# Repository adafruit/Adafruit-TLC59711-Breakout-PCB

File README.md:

# PCB for the Adafruit TLC59711 12-LED PWM breakout board

<a href="http://www.adafruit.com/products/1455"><br/>Click here to purchase one from the Adafruit shop</a>

For all of you out there who want to control 12 channels of PWM, we salute you! We also would like you to check out this breakout board for the TLC59711 PWM driver chip. This chip can control 12 separate channels of 16-bit PWM output. This is the highest-resolution PWM board we've seen! Designed (and ideal) for precision LED control, this board is not good for driving servos. If you need to drive servos, [we have a controller for that over here](http://www.adafruit.com/products/815).

Only two "SPI" pins are required to send data (our Arduino library shows how to to use any digital microcontroller pins). Best of all, the design is completely chainable. As long as there's enough power for all the boards you can chain as many as you'd like, like a little trail of blue PCBs stretching out into the sunset. Each of the 12 outputs are constant-current and open drain. You can drive multiple LEDs in series, with a V+ anode supply of up to 17V. If you want to drive something that requires a digital input, you must use a pullup resistor from the drive pin to your logic level to create the full waveform.

One resistor is used to set the current for each of the outputs, the constant current means that the LED brightness doesn't vary if the power supply dips. We use a 3.3K resistor for about 15mA but you can solder a thru-hole resistor over it if you'd like to change that value. Check the [TLC59711 datasheet](http://www.adafruit.com/datasheets/tlc59711.pdf) for details on resistor-to-current values. There's also a handy on-chip 3.3V regulator which you can use if you need a logic level regulator.

We include a few extras to make this board easy to use: a green power-good LED, four mounting holes and a current-set resistor. A bit of 0.1" header is also included so you can solder it on and plug into a breadboard.

To use: Power V+ with 5-17VDC, and connect ground to the common ground. Then send 3-5V logic SPI data on DIN (data in) and CLK (clock). Our Arduino library will get you started with blinking LEDs, install it and run the example code with the noted pin configuration.

There's a typo in the silkscreen, the second R0 should be R1 - but you knew that already!

## License

Adafruit invests time and resources providing this open source design, 
please support Adafruit and open-source hardware by purchasing 
products from Adafruit!

Designed by Adafruit Industries.  
Creative Commons Attribution, Share-Alike license, check license.txt for more information
All text above must be included in any redistribution

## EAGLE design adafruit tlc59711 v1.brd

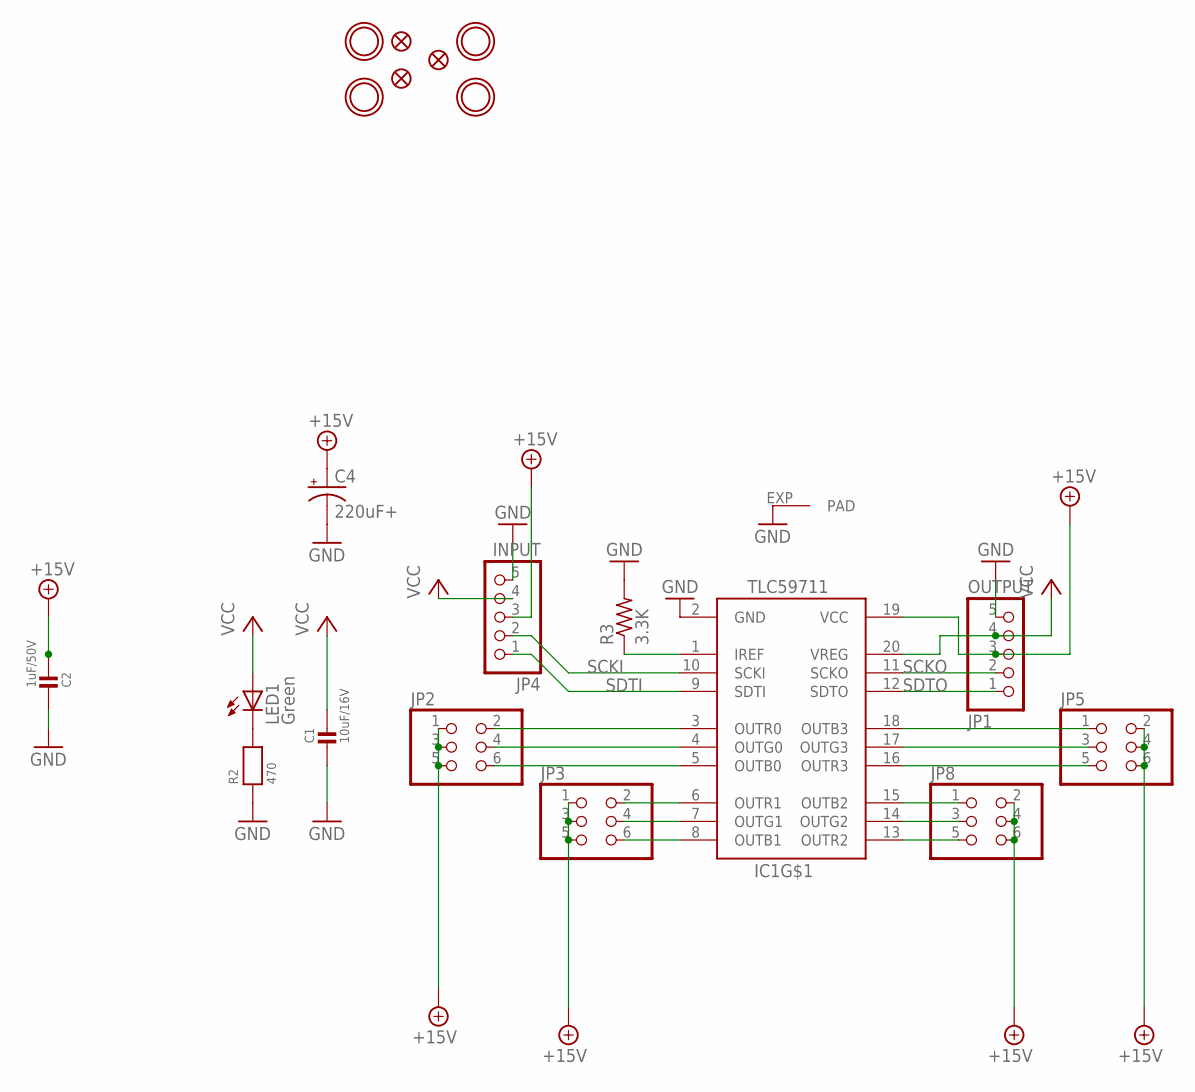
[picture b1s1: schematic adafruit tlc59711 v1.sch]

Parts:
C1: 10uF/16V; 0805
C2: 1uF/50V; 0805
C4: 220uF+; E2,5-7
FID1, FID2, FID3: FIDUCIAL""; FIDUCIAL_1MM
IC1: TLC59711; HTSSOP20DAP
JP1: OUTPUT; 1X05_ROUND_70
JP2, JP3, JP5, JP8: HEADER-2X3; 2X03_ROUND_70MIL
JP4: INPUT; 1X05_ROUND_70
LED1: Green; CHIP-LED0805
R2: 470; 0805
R3: 3.3K; 0805-THM-7
U$1, U$2, U$3, U$4: MOUNTINGHOLE2.5; MOUNTINGHOLE_2.5_PLATED

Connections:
+15V: C2.1, C4.+, IC1.19 (VCC), JP1.3, JP2.1, JP2.3, JP2.5, JP3.1, JP3.3, JP3.5, JP4.3, JP5.2, JP5.4, JP5.6, JP8.2, JP8.4, JP8.6
GND: C1.2, C2.2, C4.-, IC1.2 (GND), IC1.EXP (PAD), JP1.5, JP4.5, R2.1, R3.2
unnamed: LED1.C, R2.2
unnamed: IC1.1 (IREF), R3.1
unnamed: IC1.3 (OUTR0), JP2.2
unnamed: IC1.4 (OUTG0), JP2.4
unnamed: IC1.5 (OUTB0), JP2.6
unnamed: IC1.6 (OUTR1), JP3.2
unnamed: IC1.7 (OUTG1), JP3.4
unnamed: IC1.8 (OUTB1), JP3.6
unnamed: IC1.15 (OUTB2), JP8.1
unnamed: IC1.14 (OUTG2), JP8.3
unnamed: IC1.13 (OUTR2), JP8.5
unnamed: IC1.18 (OUTB3), JP5.1
unnamed: IC1.17 (OUTG3), JP5.3
unnamed: IC1.16 (OUTR3), JP5.5
SCKI: IC1.10 (SCKI), JP4.2
SCKO: IC1.11 (SCKO), JP1.2
SDTI: IC1.9 (SDTI), JP4.1
SDTO: IC1.12 (SDTO), JP1.1
VCC: C1.1, IC1.20 (VREG), JP1.4, JP4.4, LED1.A

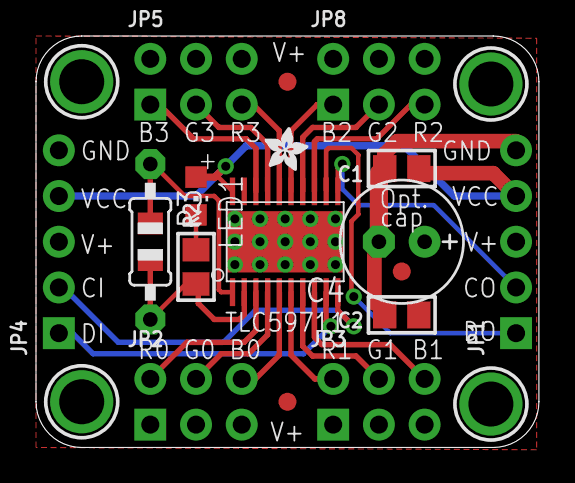
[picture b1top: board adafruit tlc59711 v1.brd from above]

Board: 2 copper layers, 27.9 x 22.9 mm, 22 parts (1 on the bottom side), 21 nets.

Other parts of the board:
U$7: ADAFRUIT_2.5MM
U$8: ADAFRUIT_3.5MM

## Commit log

2013-09-16 wooot
2019-05-08 readme + image

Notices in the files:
parts and their libraries:
microbuilder: This work is placed in the public domain, and may be freely used for commercial and non-commercial work with the following conditions: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
